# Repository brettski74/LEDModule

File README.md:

# LED Module
This is a design for a simple 3-LED lighting module that I designed for using in my 3D
printer enclosure. It uses CREE J2835 Series LEDs and runs on 11-14V input voltage, so
should run just fine off the 12V supply of many 3D printers.s

The design uses a simple two-transistor current regulator to set the LED current and
hold it steady across the entire input voltage range. The three LEDs are placed in
series and the LED current is set by R2, R3, R4 and R5. Multiple resistors are used to
handle the power dissipation without resorting to more expensive higher power SMD
resistors. Typical setup is to use 3 x 91k resistors for R2, R3 and R4 and leave R5
open. This gives a roughly 30 ohm shunt which gives a roughly 20mA LED current. If you
want to set a different LED current, you can alter the resistors used for R2, R3, R4
and R5, which are placed in parallel and form the shunt resistor of the regulator. The
LED current can be approximated by the formula:

    0.6V / Rshunt

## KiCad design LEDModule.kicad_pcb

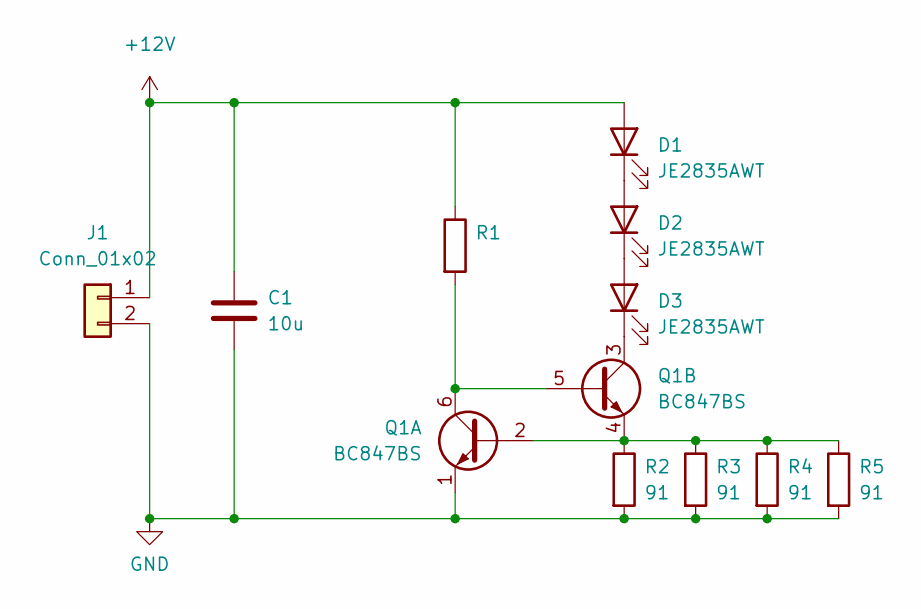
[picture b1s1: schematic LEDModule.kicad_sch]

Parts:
C1: 10u; C_0805_2012Metric
D1, D2, D3: JE2835AWT; LED_Cree-J-Series
J1: Conn_01x02; TE-HPI-1x2x2mm-1775469-2
Q1: BC847BS; SOT-363_SC-70-6
R1: (no value)
R2, R3, R4, R5: 91; R_1206_3216Metric

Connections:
+12V: C1.1, D1.2 (A), J1.1, R1.1
GND: C1.2, J1.2, Q1.1 (E1), R2.2, R3.2, R4.2, R5.2
unnamed: D1.1 (K), D2.2 (A)
unnamed: D2.1 (K), D3.2 (A)
unnamed: D3.1 (K), Q1.3 (C2)
unnamed: Q1.2 (B1), Q1.4 (E2), R2.1, R3.1, R4.1, R5.1
unnamed: Q1.5 (B2), Q1.6 (C1), R1.2

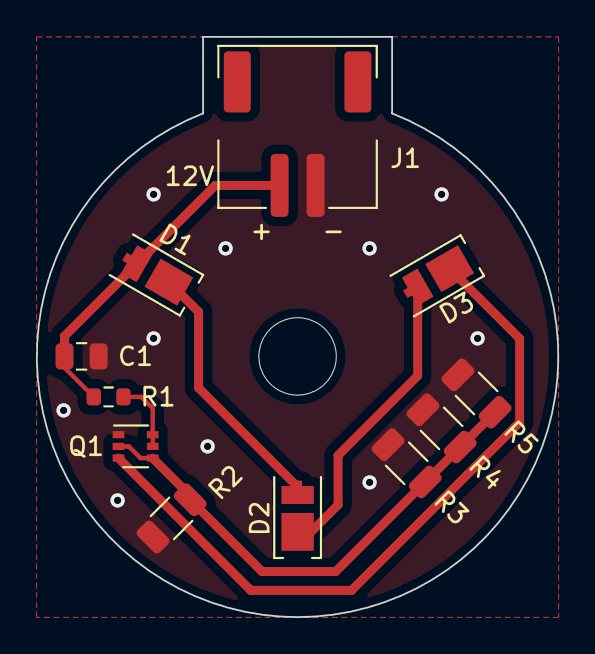
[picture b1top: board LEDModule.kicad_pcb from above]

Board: 2 copper layers, 29.0 x 32.2 mm, 11 parts (0 on the bottom side), 7 nets.

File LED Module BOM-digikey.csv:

Index,Manufacturer Part Number,Manufacturer Name,Description,Requested Quantity 1,Pack Quantity 1,Pack Type 1,Digi-Key Part Number 1,Unit Price 1,Extended Price 1,Minimum Order Quantity 1,Requested Part Number,Datasheet,Reference Designator,Image
1,JE2835AWT-00-0000-0B0A0HG765E,"CreeLED, Inc.",LED WHT CRI 80 6500K JE2835 3V,3,3,Cut Tape (CT),JE2835AWT-00-0000-0B0A0HG765ECT-ND,0.16,$0.48,1,JE2835AWT-00-0000-0B0A0HG765ECT-ND,https://media.digikey.com/pdf/Data%20Sheets/CREE%20Power/J_S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,"D1,D2,D3",https://media.digikey.com/Photos/Cree%20Photos/Cree-J-Series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
2,BC847BSHE3-TP,Micro Commercial Co,DUAL NPN SMALL SIGNAL TRANSISTOR,1,1,Cut Tape (CT),353-BC847BSHE3-TPCT-ND,0.36,$0.36,1,353-BC847BSHE3-TPCT-ND,https://www.mccsemi.com/pdf/Products/BC847BSHE3(SOT-363).pdf,Q1,
3,RMCF1206FT91R0,Stackpole Electronics Inc,RES 91 OHM 1% 1/4W 1206,3,3,Cut Tape (CT),RMCF1206FT91R0CT-ND,0.16,$0.48,1,RMCF1206FT91R0CT-ND,https://www.seielect.com/catalog/sei-rmcf_rmcp.pdf,"R2,R3,R4",https://media.digikey.com/Renders/Stackpole%20Renders/1206.jpg
4,1775469-2,TE Connectivity AMP Connectors,CONN HEADER SMD R/A 2POS 2MM,1,1,Cut Tape (CT),A100080CT-ND,1.36,$1.36,1,A100080CT-ND,https://www.te.com/commerce/DocumentDelivery/DDEController?A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,J1,https://media.digikey.com/Photos/Tyco%20Amp%20Photos/1775469-2.jpg
5,RMCF0603FT100K,Stackpole Electronics Inc,RES 100K OHM 1% 1/10W 0603,1,1,Cut Tape (CT),RMCF0603FT100KCT-ND,0.16,$0.16,1,RMCF0603FT100KCT-ND,https://www.seielect.com/catalog/sei-rmcf_rmcp.pdf,R1,https://media.digikey.com/Renders/Stackpole%20Renders/0603.jpg
6,CL21B105KOFNNNE,Samsung Electro-Mechanics,CAP CER 1UF 16V X7R 0805,1,1,Cut Tape (CT),1276-1026-1-ND,0.15,$0.15,1,CL21B105KOFNNNE,http://www.samsungsem.com/kr/support/product-search/mlcc/CL2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,C1,https://media.digikey.com/Renders/Samsung%20Electro-Mechanic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

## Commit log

2022-12-19 Initial commit of version 0.0 submitted to JLCPCB. Gerber files suitable for JLCPCB manufacture.
2022-12-19 Added BSD Licence file.
2022-12-19 Added README.md
2023-02-24 Updated package size of R1. Added LCSC BOM.
